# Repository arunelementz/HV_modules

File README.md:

# HV_Module for GM tubes

## Getting started

To make it easy for you to get started with GitLab, here's a list of recommended next steps.

Already a pro? Just edit this README.md and make it your own. Want to make it easy? [Use the template at the bottom](#editing-this-readme)!

## Add your files

- [ ] [Create](https://docs.gitlab.com/ee/user/project/repository/web_editor.html#create-a-file) or [upload](https://docs.gitlab.com/ee/user/project/repository/web_editor.html#upload-a-file) files
- [ ] [Add files using the command line](https://docs.gitlab.com/topics/git/add_files/#add-files-to-a-git-repository) or push an existing Git repository with the following command:

```
cd existing_repo
git remote add origin https://gitlab.com/arunelementz/hv_module-for-gm-tubes.git
git branch -M main
git push -uf origin main
```

## Integrate with your tools

- [ ] [Set up project integrations](https://gitlab.com/arunelementz/hv_module-for-gm-tubes/-/settings/integrations)

## Collaborate with your team

- [ ] [Invite team members and collaborators](https://docs.gitlab.com/ee/user/project/members/)
- [ ] [Create a new merge request](https://docs.gitlab.com/ee/user/project/merge_requests/creating_merge_requests.html)
- [ ] [Automatically close issues from merge requests](https://docs.gitlab.com/ee/user/project/issues/managing_issues.html#closing-issues-automatically)
- [ ] [Enable merge request approvals](https://docs.gitlab.com/ee/user/project/merge_requests/approvals/)
- [ ] [Set auto-merge](https://docs.gitlab.com/user/project/merge_requests/auto_merge/)

## Test and Deploy

Use the built-in continuous integration in GitLab.

- [ ] [Get started with GitLab CI/CD](https://docs.gitlab.com/ee/ci/quick_start/)
- [ ] [Analyze your code for known vulnerabilities with Static Application Security Testing (SAST)](https://docs.gitlab.com/ee/user/application_security/sast/)
- [ ] [Deploy to Kubernetes, Amazon EC2, or Amazon ECS using Auto Deploy](https://docs.gitlab.com/ee/topics/autodevops/requirements.html)
- [ ] [Use pull-based deployments for improved Kubernetes management](https://docs.gitlab.com/ee/user/clusters/agent/)
- [ ] [Set up protected environments](https://docs.gitlab.com/ee/ci/environments/protected_environments.html)

***

# Editing this README

When you're ready to make this README your own, just edit this file and use the handy template below (or feel free to structure it however you want - this is just a starting point!). Thanks to [makeareadme.com](https://www.makeareadme.com/) for this template.

## Suggestions for a good README

Every project is different, so consider which of these sections apply to yours. The sections used in the template are suggestions for most open source projects. Also keep in mind that while a README can be too long and detailed, too long is better than too short. If you think your README is too long, consider utilizing another form of documentation rather than cutting out information.

## Name
Choose a self-explaining name for your project.

## Description
Let people know what your project can do specifically. Provide context and add a link to any reference visitors might be unfamiliar with. A list of Features or a Background subsection can also be added here. If there are alternatives to your project, this is a good place to list differentiating factors.

## Badges
On some READMEs, you may see small images that convey metadata, such as whether or not all the tests are passing for the project. You can use Shields to add some to your README. Many services also have instructions for adding a badge.

## Visuals
Depending on what you are making, it can be a good idea to include screenshots or even a video (you'll frequently see GIFs rather than actual videos). Tools like ttygif can help, but check out Asciinema for a more sophisticated method.

## Installation
Within a particular ecosystem, there may be a common way of installing things, such as using Yarn, NuGet, or Homebrew. However, consider the possibility that whoever is reading your README is a novice and would like more guidance. Listing specific steps helps remove ambiguity and gets people to using your project as quickly as possible. If it only runs in a specific context like a particular programming language version or operating system or has dependencies that have to be installed manually, also add a Requirements subsection.

## Usage
Use examples liberally, and show the expected output if you can. It's helpful to have inline the smallest example of usage that you can demonstrate, while providing links to more sophisticated examples if they are too long to reasonably include in the README.

## Support
Tell people where they can go to for help. It can be any combination of an issue tracker, a chat room, an email address, etc.

## Roadmap
If you have ideas for releases in the future, it is a good idea to list them in the README.

## Contributing
State if you are open to contributions and what your requirements are for accepting them.

For people who want to make changes to your project, it's helpful to have some documentation on how to get started. Perhaps there is a script that they should run or some environment variables that they need to set. Make these steps explicit. These instructions could also be useful to your future self.

You can also document commands to lint the code or run tests. These steps help to ensure high code quality and reduce the likelihood that the changes inadvertently break something. Having instructions for running tests is especially helpful if it requires external setup, such as starting a Selenium server for testing in a browser.

## Authors and acknowledgment
Show your appreciation to those who have contributed to the project.

## License
For open source projects, say how it is licensed.

## Project status
If you have run out of energy or time for your project, put a note at the top of the README saying that development has slowed down or stopped completely. Someone may choose to fork your project or volunteer to step in as a maintainer or owner, allowing your project to keep going. You can also make an explicit request for maintainers.

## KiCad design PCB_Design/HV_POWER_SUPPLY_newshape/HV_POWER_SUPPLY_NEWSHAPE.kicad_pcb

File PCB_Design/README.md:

## HV Schematic and PCB Design Notes

- Schematic is the same as the original **CN0536 board**, including all annotations.
- **Sound notification** is **not included** in the PCB design.
- **BOM** is based on the original **CN0536 BOM**.
- **R19 and R20** are changed to **30 MΩ**  
  - Note: CN0536 BOM specifies **30 MΩ**, but a **different value appears in the schematic** and needs verification.
- **CN0536 stack arrangement** differs and should follow the reference shown.

- **Footprints to be confirmed**:
  - L1  
  - R9  
  - U1  
  - U5
- **Edge cuts** and **high-voltage trace clearance** need to be confirmed.
- **Potentiometer pin numbering** in schematic symbols has been checked.
- **Polygons** are used for drawing copper zones.

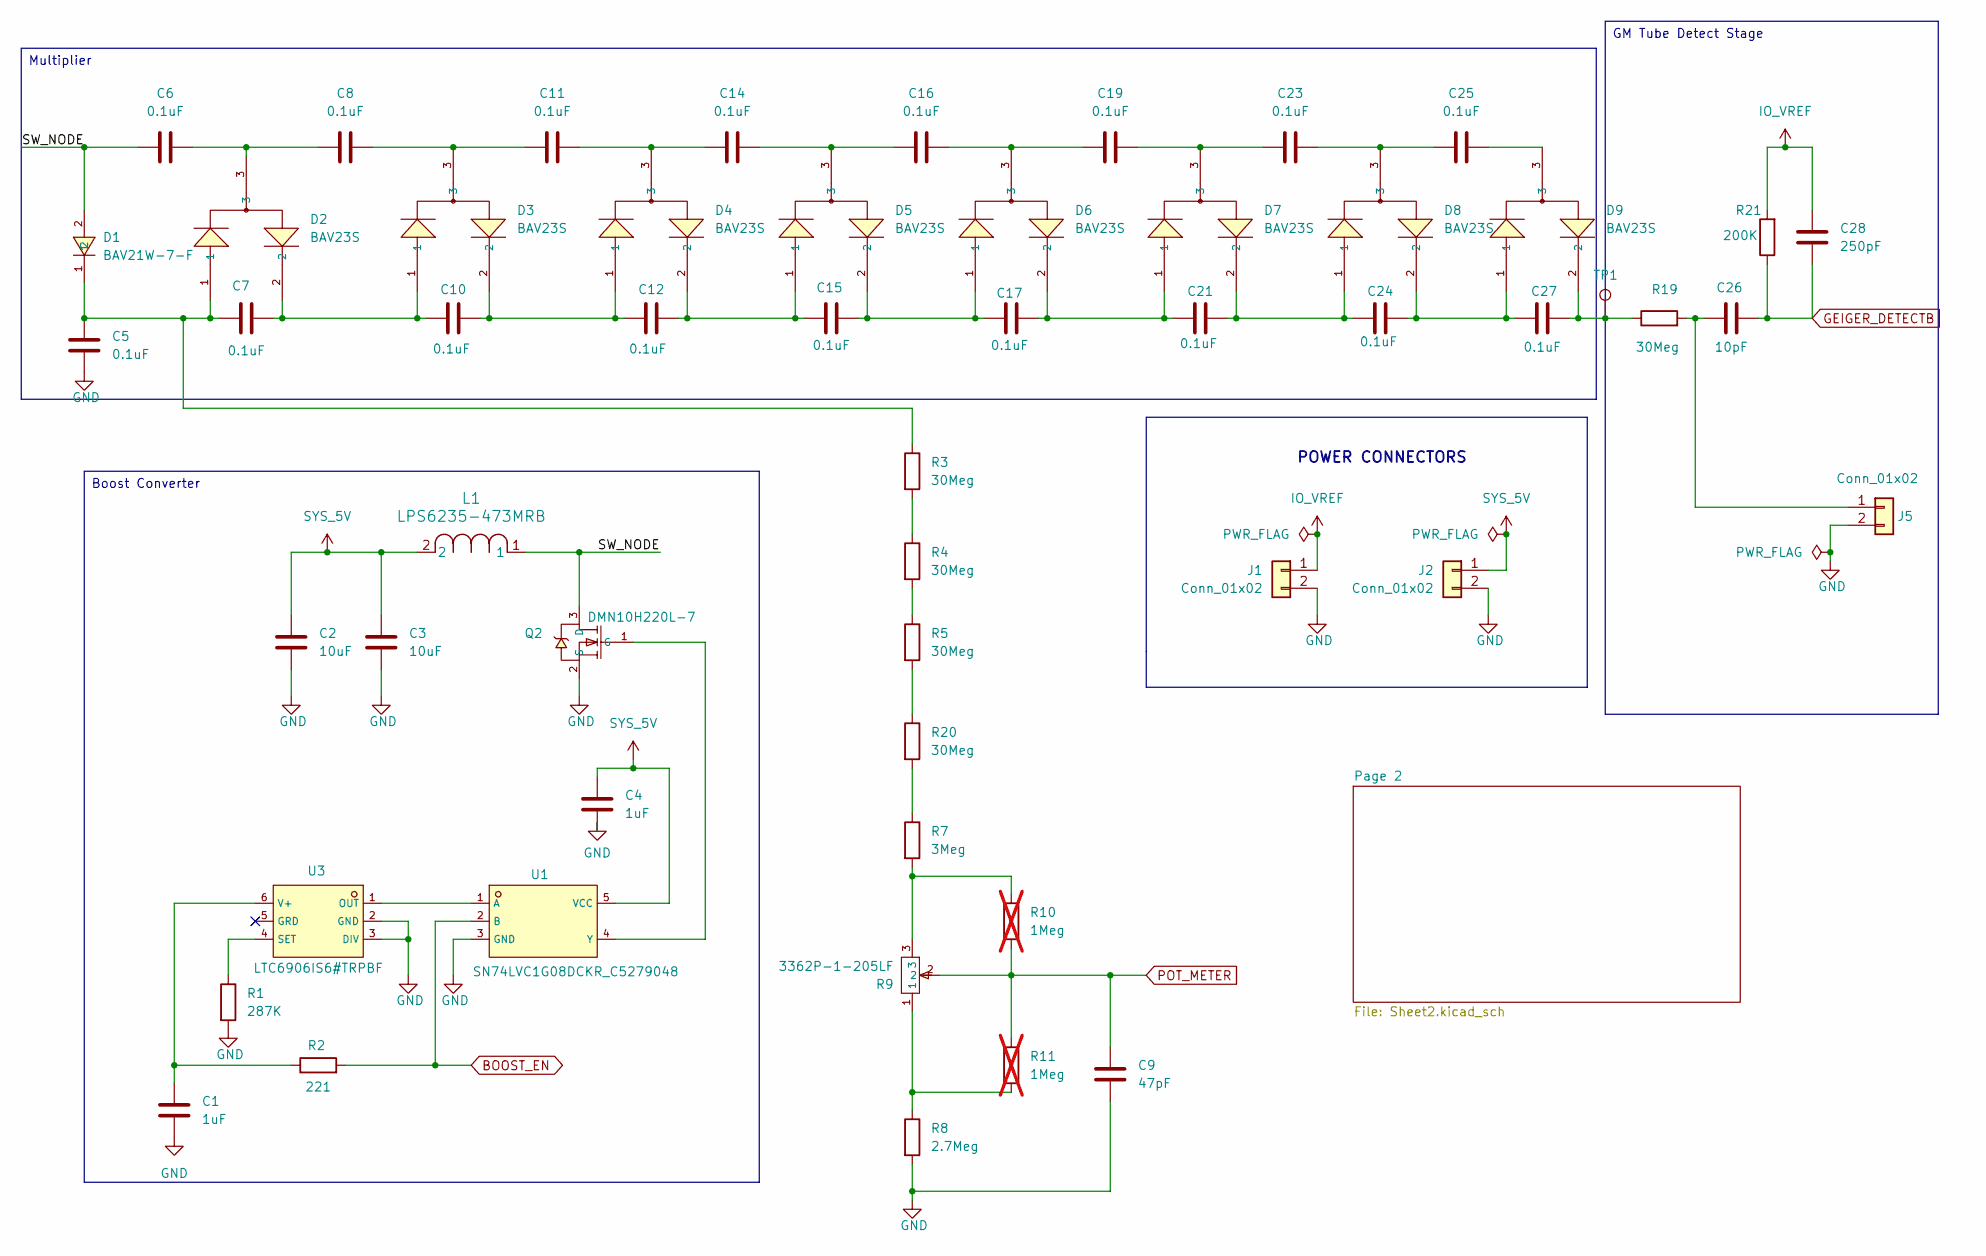
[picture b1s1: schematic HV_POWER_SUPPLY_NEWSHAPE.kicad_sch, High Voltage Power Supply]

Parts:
C1, C4: 1uF; C_0603_1608Metric; manufacturer Part Number 0603YC105KAT2A; LCSC C4153100
C2, C3: 10uF; C_0805_2012Metric; manufacturer Part Number GRM21BR61C106KE15L; LCSC C77075
C5, C6, C7, C8, C10, C11, C12, C14, C15, C16, C17, C19, C21, C23, C24, C25, C27: 0.1uF; C_1206_3216Metric; manufacturer Part Number 12061C104JAT2A; LCSC C597455
C9: 47pF; C_0603_1608Metric; manufacturer Part Number C0603C470K5RACAUTO; LCSC C2169937
C26: 10pF; C_1206_3216Metric; manufacturer Part Number CGA1206C0G100J102MT; LCSC C22374878
C28: 250pF; C_0603_1608Metric; manufacturer Part Number 06033A251JAT2A; Digikey part number 478-11806-2-ND
D1: BAV21W-7-F; SOD-123_L2.8-W1.8-LS3.7-RD; manufacturer Part Number BAV21WS-7-F; LCSC C155214
D2, D3, D4, D5, D6, D7, D8, D9: BAV23S; BAV23S_SOT-23-3_L2.9-W1.6-P1.90-LS2.8-BR; manufacturer Part Number BAV23S; LCSC C151049
J1, J2, J5: Conn_01x02; PinHeader_1x02_P2.54mm_Vertical; manufacturer Part Number PH1-02-UA; LCSC C5828287
L1: LPS6235-473MRB; LPS6235473MRB; manufacturer Part Number LPS6235-473MRC; Mouser Number 994-LPS6235-473MRB
Q2: DMN10H220L-7; SOT-23-3_L2.9-W1.6-P1.90-LS2.8-BR; manufacturer Part Number DMN10H220L-7; LCSC C102615
R1: 287K; R_0603_1608Metric; manufacturer Part Number RC0603FR-07287KL; LCSC C245944
R2: 221; R_0805_2012Metric; manufacturer Part Number TP0805B221RP0510Z; LCSC C5184183
R3, R4, R5, R19, R20: 30Meg; R_0805_2012Metric; manufacturer Part Number HVCB0805FDC30M0; LCSC HVCB0805FDC30M0
R7: 3Meg; R_0603_1608Metric; manufacturer Part Number CRCW06033M00FKEA; LCSC C4299696
R8: 2.7Meg; R_0603_1608Metric; manufacturer Part Number FRC0805F2704TS; LCSC C403468
R9: 3362P-1-205LF; RES-ADJ-TH_3362P; manufacturer Part Number 3362P-1-205LF; LCSC C124582
R10, R11: 1Meg; R_0603_1608Metric; manufacturer Part Number RC0805FR-071ML; LCSC C107700; not fitted
R21: 200K; R_0603_1608Metric; manufacturer Part Number ERJ3EKF2003V; LCSC C118142
TP1: TestPoint; TestPoint_Pad_1.0x1.0mm
U1: SN74LVC1G08DCKR_C5279048; SC-70-5_L2.0-W1.3-P0.65-LS2.1-BR; manufacturer Part Number SN74LVC1G08DCKR; LCSC C7832
U3: LTC6906IS6#TRPBF; TSOT-23-6_L2.9-W1.6-P0.95-LS2.8-BR; manufacturer Part Number LTC6906IS6#TRMPBF; LCSC C581017

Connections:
/SW_NODE: C6.1, D1.2, L1.1, Q2.3 (D)
BOOST_EN: R2.2, U1.2 (B); also elsewhere on the board
GEIGER_DETECTB: C26.2, C28.1, R21.1; also elsewhere on the board
GND: C1.2, C2.2, C3.2, C4.2, C5.2, C9.2, J1.2, J2.2, J5.2, Q2.2 (S), R1.2, R8.2, U1.3 (GND), U3.2 (GND), U3.3 (DIV); also elsewhere on the board
IO_VREF: C28.2, J1.1, R21.2; also elsewhere on the board
unnamed: C5.1, C7.1, D1.1, D2.1, R3.1
unnamed: C6.2, C8.1, D2.3
unnamed: C7.2, C10.1, D2.2, D3.1
unnamed: C10.2, C12.1, D3.2, D4.1
unnamed: C8.2, C11.1, D3.3
unnamed: C11.2, C14.1, D4.3
unnamed: C12.2, C15.1, D4.2, D5.1
unnamed: C14.2, C16.1, D5.3
unnamed: C15.2, C17.1, D5.2, D6.1
unnamed: C16.2, C19.1, D6.3
unnamed: C17.2, C21.1, D6.2, D7.1
unnamed: C19.2, C23.1, D7.3
unnamed: C21.2, C24.1, D7.2, D8.1
unnamed: C23.2, C25.1, D8.3
unnamed: C24.2, C27.1, D8.2, D9.1
unnamed: C25.2, D9.3
unnamed: C27.2, D9.2, R19.1, TP1.1
unnamed: C26.1, J5.1, R19.2
unnamed: Q2.1 (G), U1.4 (Y)
unnamed: R3.2, R4.1
unnamed: R4.2, R5.1
unnamed: R7.2, R9.3, R10.1
unnamed: R8.1, R9.1, R11.2
unnamed: R5.2, R20.1
unnamed: R7.1, R20.2
unnamed: U1.1 (A), U3.1 (OUT)
unnamed: R1.1, U3.4 (SET)
unnamed: C1.1, R2.1, U3.6 (V+)
POT_METER: C9.1, R9.2, R10.2, R11.1; also elsewhere on the board
SYS_5V: C2.1, C3.1, C4.1, J2.1, L1.2, U1.5 (VCC); also elsewhere on the board

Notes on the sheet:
POWER CONNECTORS
Boost Converter
GM Tube Detect Stage
Multiplier

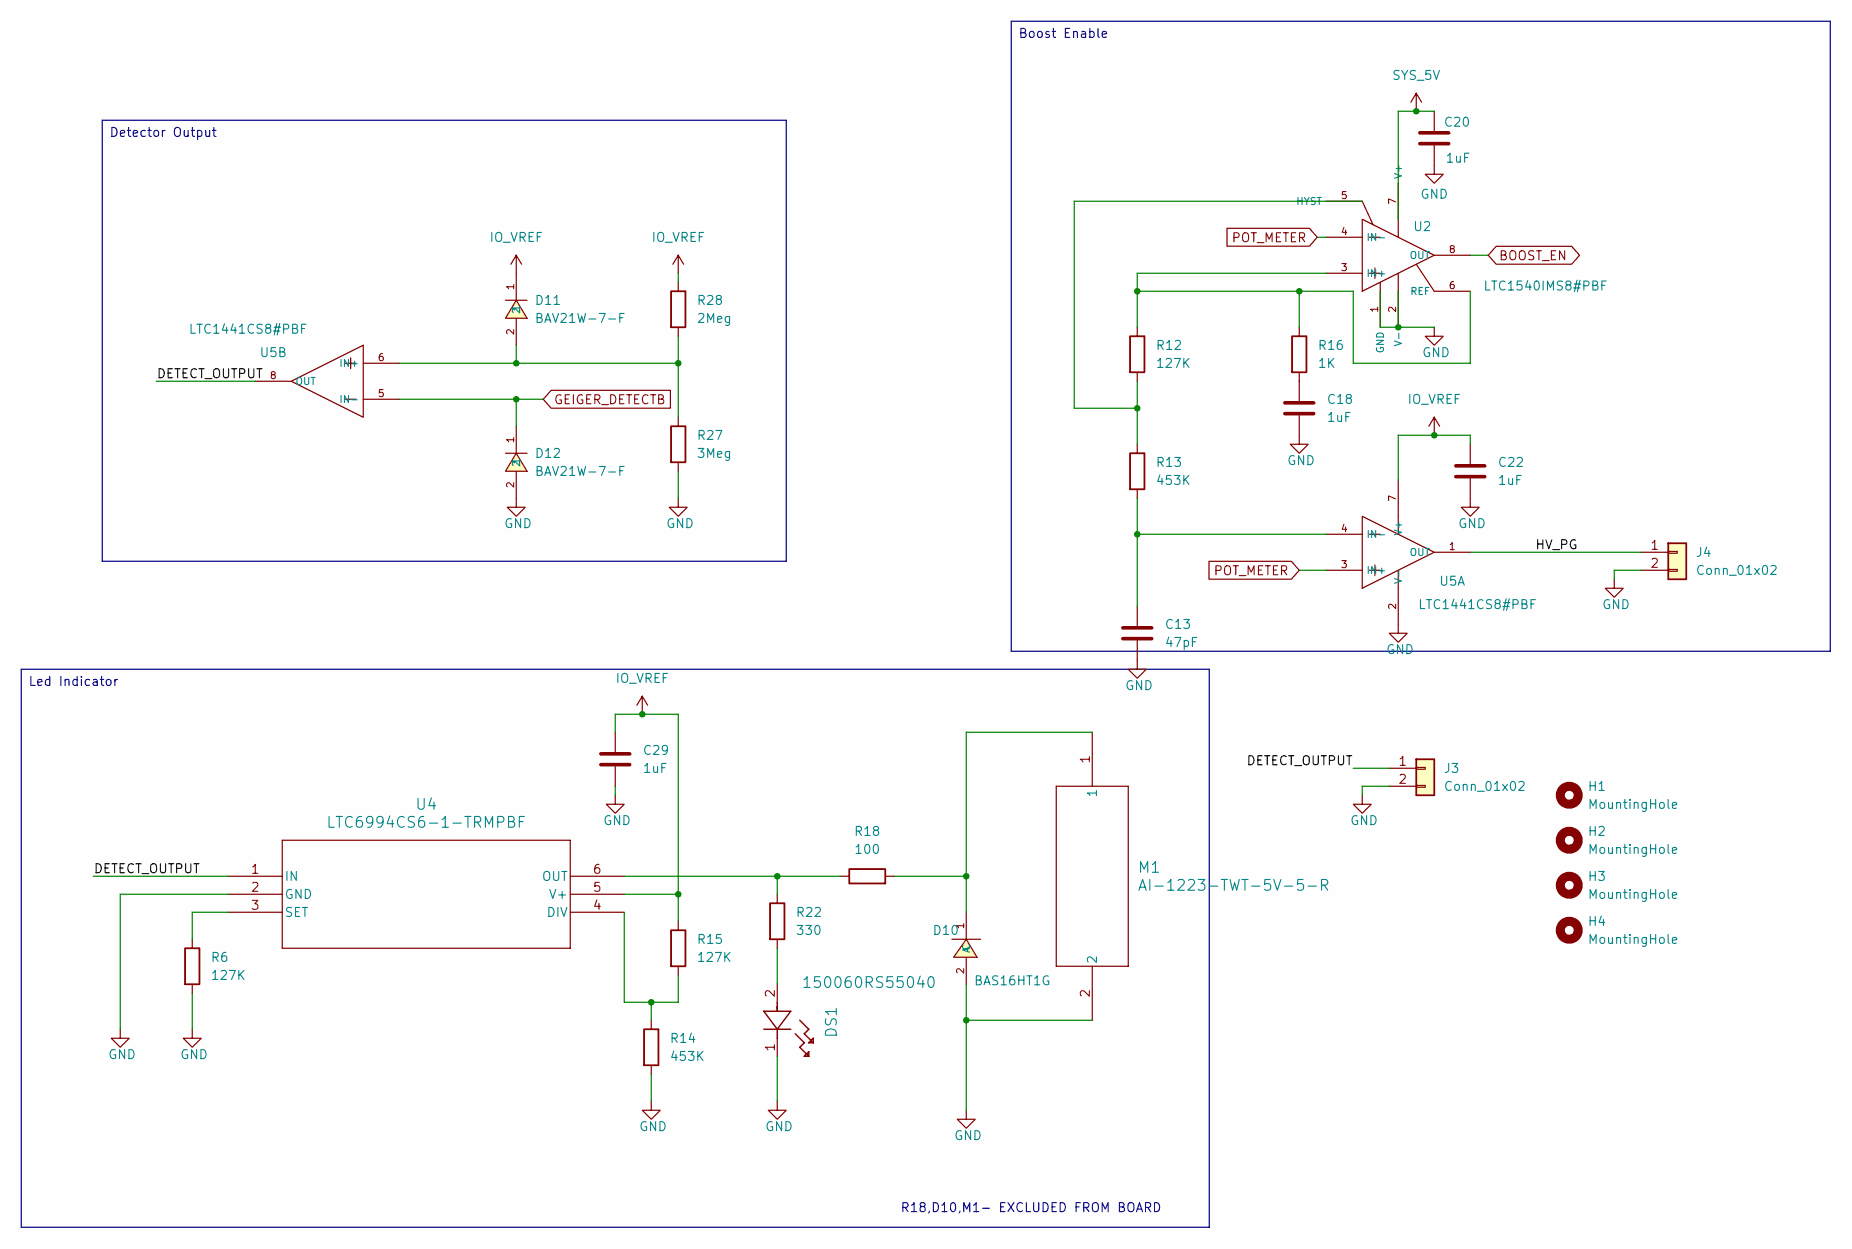
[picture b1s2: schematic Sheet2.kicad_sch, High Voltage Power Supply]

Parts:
C13: 47pF; C_0603_1608Metric; manufacturer Part Number C0603C470K5RACAUTO; LCSC C2169937
C18, C20, C22, C29: 1uF; C_0603_1608Metric; manufacturer Part Number 0603YC105KAT2A; LCSC C4153100
D10: BAS16HT1G; SOD-323_L1.8-W1.3-LS2.5-RD; manufacturer Part Number BAS16HT1G; LCSC C131148
D11, D12: BAV21W-7-F; SOD-123_L2.8-W1.8-LS3.7-RD; manufacturer Part Number BAV21WS-7-F; LCSC C155214
DS1: 150060RS55040; LED_0603_1608Metric; manufacturer Part Number 150060RS55040; LCSC C6067128
H1, H2, H3, H4: MountingHole; MountingHole_3.2mm_M3
J3, J4: Conn_01x02; PinHeader_1x02_P2.54mm_Vertical; manufacturer Part Number PH1-02-UA; LCSC C5828287
M1: AI-1223-TWT-5V-5-R; AI-1223-TWT-5V-5-R_PUI; manufacturer Part Number AI-1223-TWT-5V-5-R; LCSC C5250722
R6, R12, R15: 127K; R_0603_1608Metric; manufacturer Part Number RC0603FR-07127KL; LCSC C245905
R13, R14: 453K; R_0603_1608Metric; manufacturer Part Number RC0603FR-07453KL; LCSC C273765
R16: 1K; R_0603_1608Metric; manufacturer Part Number RC0603FR-071KL; LCSC C22548
R18: 100; R_0603_1608Metric; manufacturer Part Number 0805W8F1000T5E; LCSC C17408
R22: 330; R_0603_1608Metric; manufacturer Part Number 0603WAJ0331T5E; LCSC C25231
R27: 3Meg; R_0603_1608Metric; manufacturer Part Number CRCW06033M00FKEA; LCSC C4299696
R28: 2Meg; R_0603_1608Metric; manufacturer Part Number RC0603FR-072ML; LCSC C114615
U2: LTC1540IMS8#PBF; MSOP-8_L3.0-W3.0-P0.65-LS4.9-BL; manufacturer Part Number LTC1540IMS8#PBF; LCSC C580397
U4: LTC6994CS6-1-TRMPBF; TSOT-23_S6_LIT; manufacturer Part Number LTC6994CS6-1#TRMPBF; LCSC C581050
U5: LTC1441CS8#PBF; SOIC-8_L4.9-W3.8-P1.27-LS6.0-BL; manufacturer Part Number LTC1441CS8#PBF; LCSC C675522

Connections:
/Page 2/DETECT_OUTPUT: J3.1, U4.1 (IN), U5.8 (OUT)
/Page 2/HV_PG: J4.1, U5.1 (OUT)
BOOST_EN: U2.8 (OUT); also elsewhere on the board
GEIGER_DETECTB: D12.1, U5.5 (IN-); also elsewhere on the board
GND: C13.2, C18.2, C20.2, C22.2, C29.2, D10.2 (A), D12.2, DS1.1, J3.2, J4.2, M1.2, R6.2, R14.2, R27.2, U2.1 (GND), U2.2 (V-), U4.2 (GND), U5.2 (V-); also elsewhere on the board
IO_VREF: C22.1, C29.1, D11.1, R15.1, R28.1, U4.5 (V+), U5.7 (V+); also elsewhere on the board
unnamed: C18.1, R16.2
unnamed: D10.1 (C), M1.1, R18.2
unnamed: DS1.2, R22.2
unnamed: R12.2, R13.1, U2.5 (HYST)
unnamed: R12.1, R16.1, U2.3 (IN+), U2.6 (REF)
unnamed: R14.1, R15.2, U4.4 (DIV)
unnamed: R18.1, R22.1, U4.6 (OUT)
unnamed: R6.1, U4.3 (SET)
unnamed: C13.1, R13.2, U5.4 (IN-)
unnamed: D11.2, R27.1, R28.2, U5.6 (IN+)
POT_METER: U2.4 (IN-), U5.3 (IN+); also elsewhere on the board
SYS_5V: C20.1, U2.7 (V+); also elsewhere on the board

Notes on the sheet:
R18,D10,M1- EXCLUDED FROM BOARD
Detector Output
Boost Enable
Led Indicator

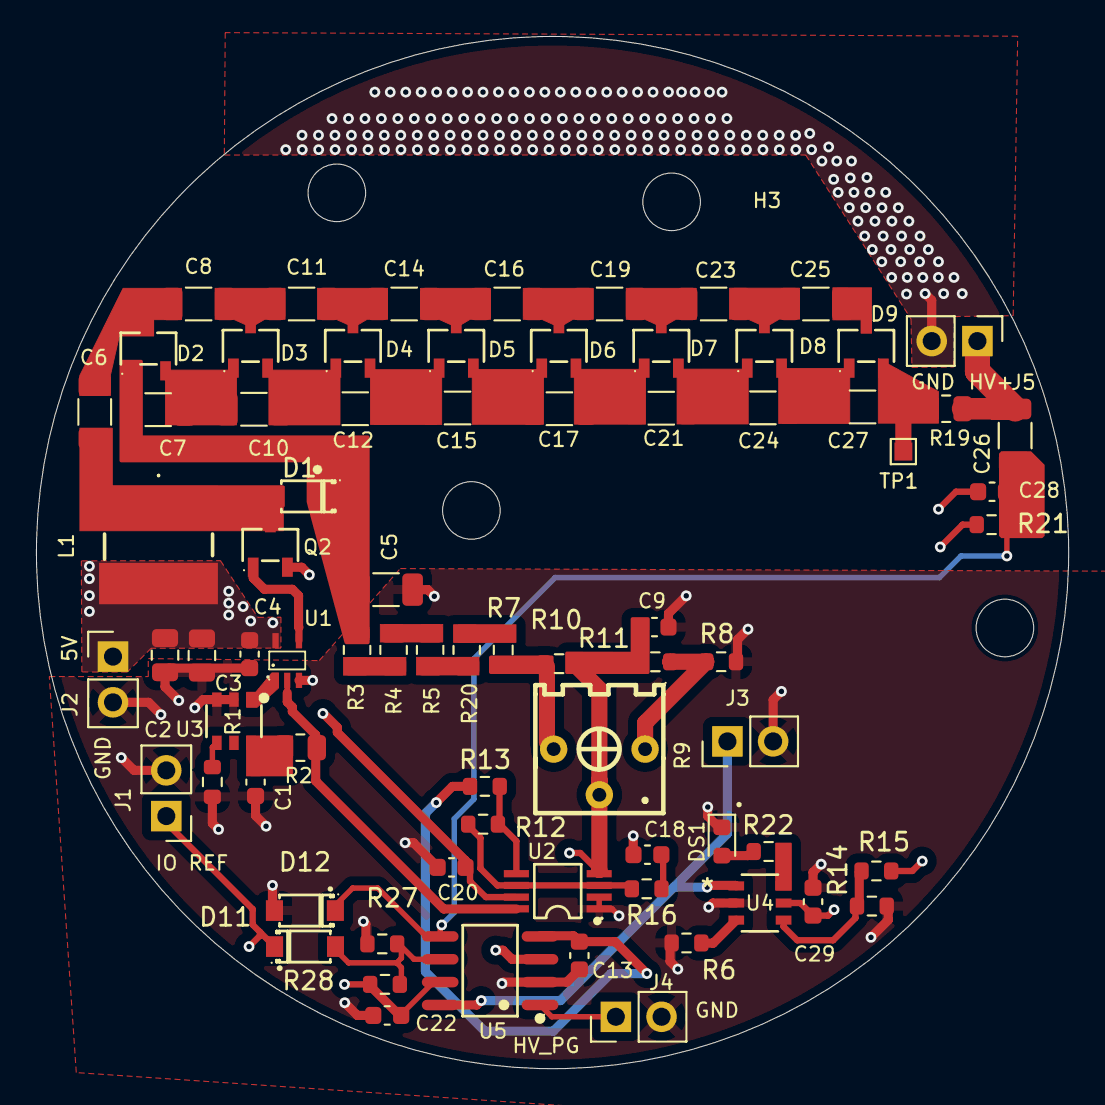
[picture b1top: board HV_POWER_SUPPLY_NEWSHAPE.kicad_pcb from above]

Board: 4 copper layers, 57.3 x 57.3 mm, 80 parts (0 on the bottom side), 46 nets.

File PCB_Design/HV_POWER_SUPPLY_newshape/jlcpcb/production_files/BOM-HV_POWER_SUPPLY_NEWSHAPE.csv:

Comment,Designator,Footprint,LCSC,Quantity
0.1uF,"C10,C11,C12,C14,C15,C16,C17,C19,C21,C23,C24,C25,C27,C5,C6,C7,C8",C_1206_3216Metric,C597455,17
10pF,C26,C_1206_3216Metric,C22374878,1
10uF,"C2,C3",C_0805_2012Metric,C77075,2
127K,"R12,R15",R_0603_1608Metric,C228282,2
127K,R6,R_0603_1608Metric,C245905,1
1K,R16,R_0603_1608Metric,C22548,1
1uF,"C1,C18,C20,C22,C29,C4",C_0603_1608Metric,C4153100,6
2.7Meg,R8,R_0603_1608Metric,C403468,1
200K,R21,R_0603_1608Metric,C118142,1
221,R2,R_0805_2012Metric,C5184183,1
250pF,C28,C_0603_1608Metric,C2169911,1
287K,R1,R_0603_1608Metric,C245944,1
2Meg,R28,R_0603_1608Metric,C114615,1
30Meg,"R19,R20,R3,R4,R5",R_0805_2012Metric,C2641377,5
330,R22,R_0603_1608Metric,C25231,1
3362P-1-205LF,R9,RES-ADJ-TH_3362P,C124582,1
3Meg,"R27,R7",R_0603_1608Metric,C4299696,2
453K,"R13,R14",R_0603_1608Metric,C273765,2
47pF,"C13,C9",C_0603_1608Metric,C2169937,2
BAV21W-7-F,"D1,D11,D12",SOD-123_L2.8-W1.8-LS3.7-RD,C155214,3
BAV23S,"D2,D3,D4,D5,D6,D7,D8,D9",BAV23S_SOT-23-3_L2.9-W1.6-P1.90-LS2.8-BR,C151049,8
Conn_01x02,"J1,J2,J3,J4,J5",PinHeader_1x02_P2.54mm_Vertical,C5828287,5
DMN10H220L-7,Q2,SOT-23-3_L2.9-W1.6-P1.90-LS2.8-BR,C102615,1
LPS6235-473MRB,L1,LPS6235473MRB,C3911705,1
LTC1441CS8#PBF,U5,SOIC-8_L4.9-W3.8-P1.27-LS6.0-BL,C675522,1
LTC1540IMS8#PBF,U2,MSOP-8_L3.0-W3.0-P0.65-LS4.9-BL,C580397,1
LTC6906IS6#TRPBF,U3,TSOT-23-6_L2.9-W1.6-P0.95-LS2.8-BR,C581017,1
LTC6994CS6-1-TRMPBF,U4,TSOT-23_S6_LIT,C581050,1
SN74LVC1G08DCKR_C5279048,U1,SC-70-5_L2.0-W1.3-P0.65-LS2.1-BR,C7832,1
TLMS1000-GS08,DS1,LED_0603_1608Metric,C2286,1
TestPoint,TP1,TestPoint_Pad_1.0x1.0mm,,1

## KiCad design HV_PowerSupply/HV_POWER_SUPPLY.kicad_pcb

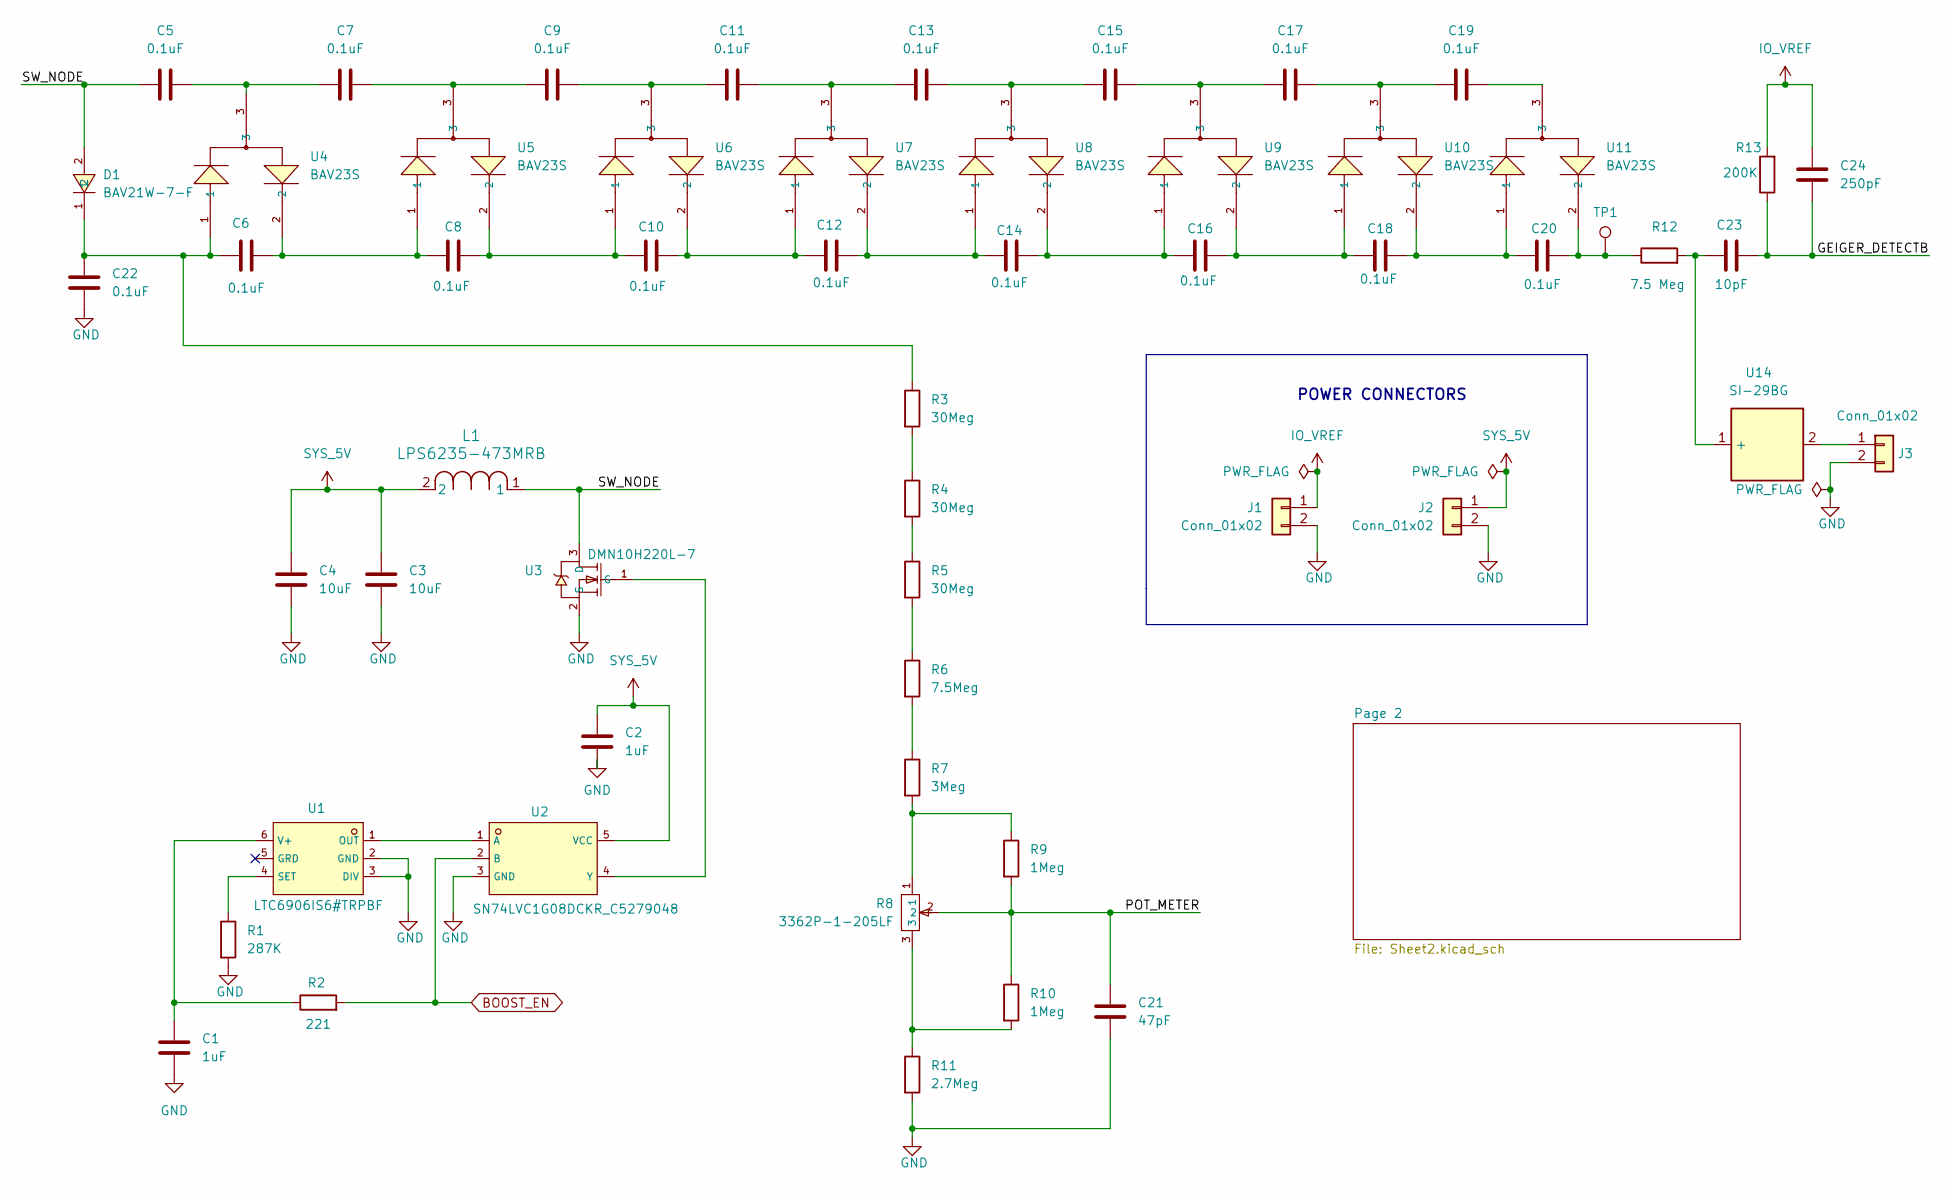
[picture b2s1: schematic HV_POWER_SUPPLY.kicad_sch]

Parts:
C1, C2: 1uF; C_0603_1608Metric; manufacturer Part Number CL10A105KB8NNNC; LCSC C15849
C3, C4: 10uF; C_0805_2012Metric; manufacturer Part Number CL21A106KAYNNNE; LCSC C15850
C5, C6, C7, C8, C9, C10, C11, C12, C13, C14, C15, C16, C17, C18, C19, C20, C22: 0.1uF; C_1206_3216Metric; manufacturer Part Number CL31B104KBCNNNC; LCSC C24497
C21: 47pF; C_0603_1608Metric; manufacturer Part Number 0603X476M6R3NT; LCSC C178330
C23: 10pF; C_1206_3216Metric; manufacturer Part Number TCC1206COG100J102DT; LCSC C377014
C24: 250pF; C_0603_1608Metric; manufacturer Part Number 06033A251JAT2A; Digikey part number 478-11806-2-ND
D1: BAV21W-7-F; SOD-323_L1.8-W1.3-LS2.5-RD; manufacturer Part Number BAV21WS-7-F; LCSC C151350
J1, J2, J3: Conn_01x02; PinHeader_1x02_P2.54mm_Vertical
L1: LPS6235-473MRB; LPS6235473MRB; manufacturer Part Number LPS6235-473MRB; Mouser Number 994-LPS6235-473MRB
R1: 287K; R_0603_1608Metric; manufacturer Part Number 0603WAF2873T5E; LCSC C22972
R2: 221; R_0805_2012Metric; manufacturer Part Number CR0805-FX-2210ELF; LCSC C204308
R3, R4, R5: 30Meg; R_0805_2012Metric; manufacturer Part Number FHW0805UC2N2KGT; LCSC C317991
R6: 7.5Meg; R_0805_2012Metric; manufacturer Part Number FRC0805J755 TS; LCSC C2933569
R7: 3Meg; R_0805_2012Metric; manufacturer Part Number FRC0805J305 TS; LCSC C2907325
R8: 3362P-1-205LF; RES-ADJ-TH_3362P; manufacturer Part Number 3362P-1-205LF; LCSC C124582
R9, R10: 1Meg; R_0805_2012Metric; manufacturer Part Number RC0805FR-071ML; LCSC C107700
R11: 2.7Meg; R_0805_2012Metric; manufacturer Part Number FRC0805F2704TS; LCSC C2933390
R12: 7.5 Meg; R_0805_2012Metric; manufacturer Part Number FRC0805J755 TS; LCSC C2933569
R13: 200K; R_0805_2012Metric; manufacturer Part Number 0805W8F2003T5E; LCSC C17539
TP1: TestPoint; TestPoint_Pad_1.0x1.0mm
U1: LTC6906IS6#TRPBF; TSOT-23-6_L2.9-W1.6-P0.95-LS2.8-BR; manufacturer Part Number LTC6906IS6#TRPBF; LCSC C689638
U2: SN74LVC1G08DCKR_C5279048; SC-70-5_L2.0-W1.3-P0.65-LS2.1-BR; manufacturer Part Number SN74LVC1G08DCKR; LCSC C5279048
U3: DMN10H220L-7; SOT-23-3_L2.9-W1.6-P1.90-LS2.8-BR; manufacturer Part Number DMN10H220L-7; LCSC C102615
U4, U5, U6, U7, U8, U9, U10, U11: BAV23S; BAV23S_SOT-23-3_L2.9-W1.6-P1.90-LS2.8-BR; manufacturer Part Number BAV23S; LCSC C44345
U14: SI-29BG

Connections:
/GEIGER_DETECTB: C23.2, C24.1, R13.1
/POT_METER: C21.1, R8.2, R9.2, R10.1
/SW_NODE: C5.1, D1.2, L1.1, U3.3 (D)
BOOST_EN: R2.2, U2.2 (B); also elsewhere on the board
GND: C1.2, C2.2, C3.2, C4.2, C21.2, C22.2, J1.2, J2.2, J3.2, R1.2, R11.2, U1.2 (GND), U1.3 (DIV), U2.3 (GND), U3.2 (S); also elsewhere on the board
IO_VREF: C24.2, J1.1, R13.2; also elsewhere on the board
unnamed: C5.2, C7.1, U4.3
unnamed: C6.2, C8.1, U4.2, U5.1
unnamed: C7.2, C9.1, U5.3
unnamed: C8.2, C10.1, U5.2, U6.1
unnamed: C10.2, C12.1, U6.2, U7.1
unnamed: C9.2, C11.1, U6.3
unnamed: C11.2, C13.1, U7.3
unnamed: C12.2, C14.1, U7.2, U8.1
unnamed: C13.2, C15.1, U8.3
unnamed: C14.2, C16.1, U8.2, U9.1
unnamed: C15.2, C17.1, U9.3
unnamed: C16.2, C18.1, U9.2, U10.1
unnamed: C17.2, C19.1, U10.3
unnamed: C18.2, C20.1, U10.2, U11.1
unnamed: C19.2, U11.3
unnamed: C20.2, R12.1, TP1.1, U11.2
unnamed: C6.1, C22.1, D1.1, R3.1, U4.1
unnamed: J3.1, U14.2
unnamed: R3.2, R4.1
unnamed: R4.2, R5.1
unnamed: R5.2, R6.1
unnamed: R6.2, R7.1
unnamed: R7.2, R8.1, R9.1
unnamed: R8.3, R10.2, R11.1
unnamed: U1.1 (OUT), U2.1 (A)
unnamed: R1.1, U1.4 (SET)
unnamed: C1.1, R2.1, U1.6 (V+)
unnamed: U2.4 (Y), U3.1 (G)
unnamed: C23.1, R12.2, U14.1 (+)
SYS_5V: C2.1, C3.1, C4.1, J2.1, L1.2, U2.5 (VCC); also elsewhere on the board

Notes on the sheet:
POWER CONNECTORS

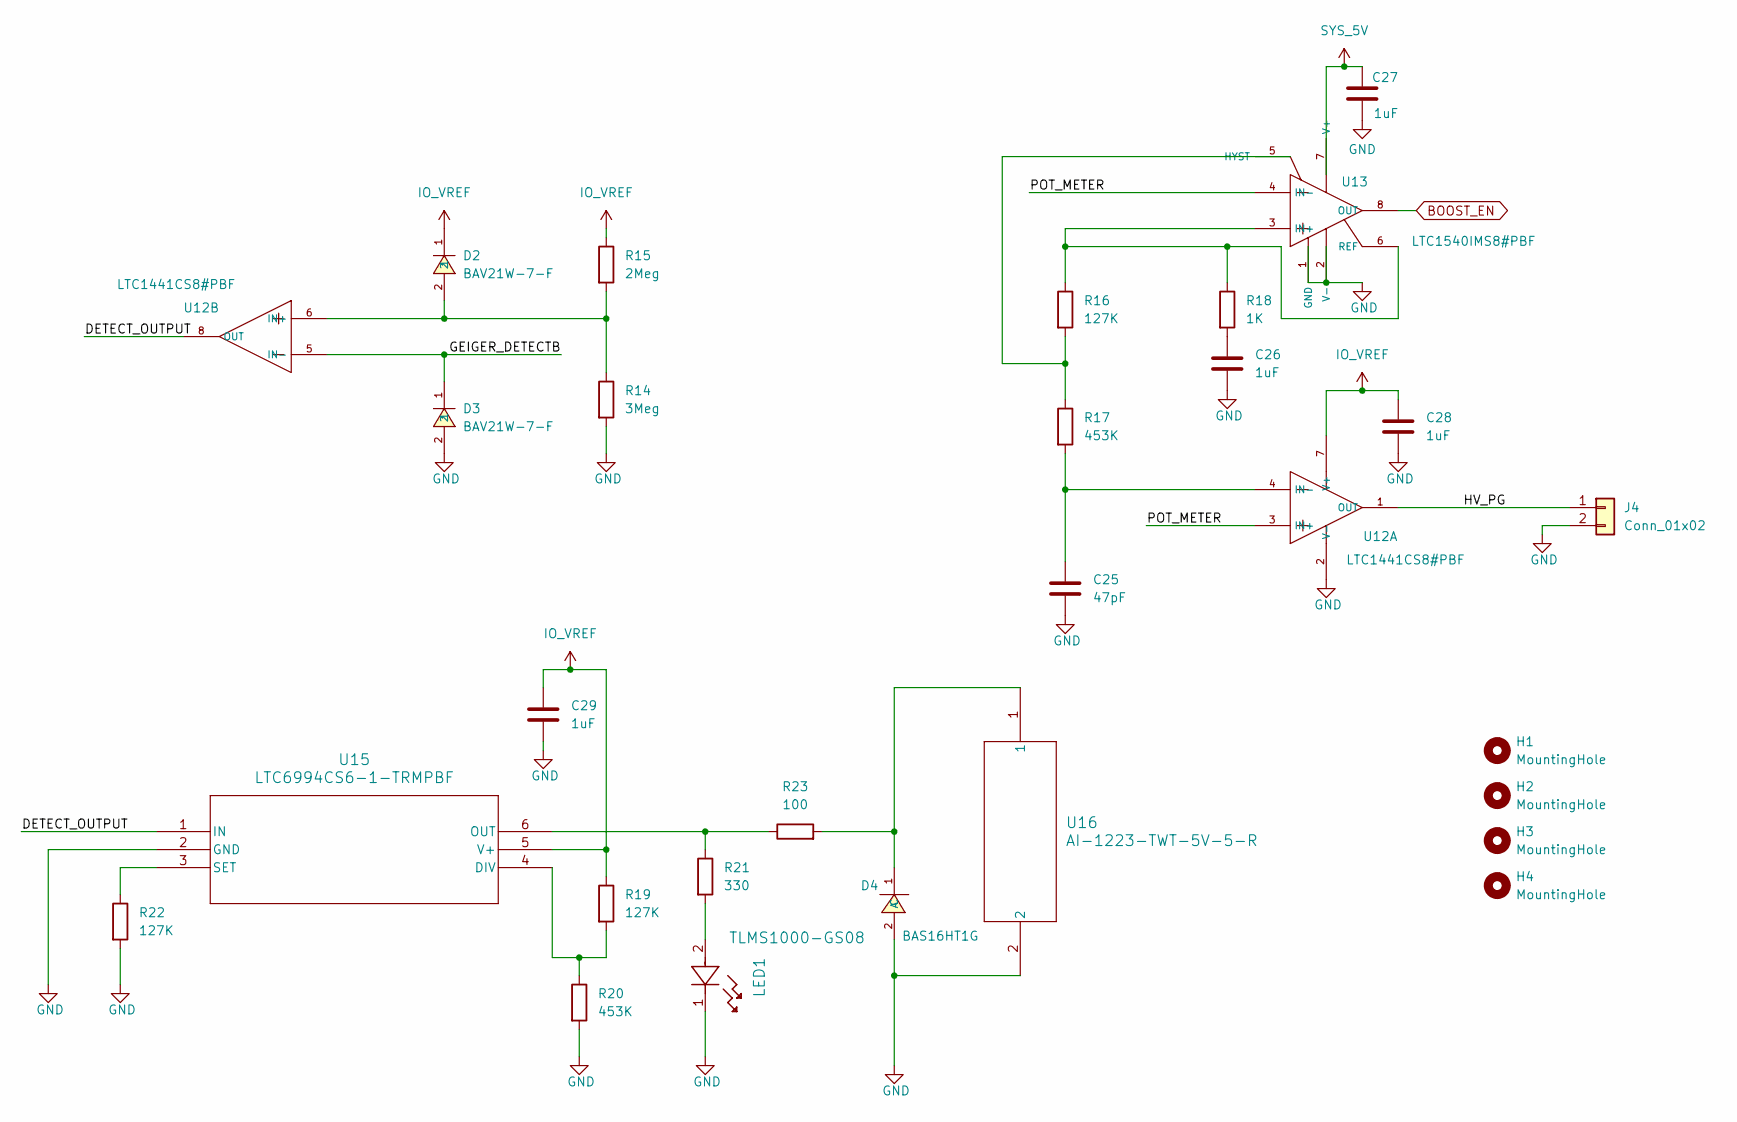
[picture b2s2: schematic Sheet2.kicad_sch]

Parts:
C25: 47pF; C_0603_1608Metric; manufacturer Part Number 0603X476M6R3NT; LCSC C178330
C26, C27, C28, C29: 1uF; C_0603_1608Metric; manufacturer Part Number CL10A105KB8NNNC; LCSC C15849
D2, D3: BAV21W-7-F; SOD-323_L1.8-W1.3-LS2.5-RD; manufacturer Part Number BAV21WS-7-F; LCSC C151350
D4: BAS16HT1G; SOD-323_L1.8-W1.3-LS2.5-RD; manufacturer Part Number BAS16HT1G; LCSC C131148
H1, H2, H3, H4: MountingHole; MountingHole_3.2mm_M3
J4: Conn_01x02; PinHeader_1x02_P2.54mm_Vertical
LED1: TLMS1000-GS08; LED_0603_1608Metric; manufacturer Part Number KT-0603R; LCSC C2286
R14: 3Meg; R_0805_2012Metric; manufacturer Part Number FRC0805J305 TS; LCSC C2907325
R15: 2Meg; R_0805_2012Metric; manufacturer Part Number 0805W8F2004T5E; LCSC C26112
R16, R19, R22: 127K; R_0805_2012Metric; manufacturer Part Number AC0805FR-07127KL; LCSC C228282
R17, R20: 453K; R_0805_2012Metric; manufacturer Part Number UNI-ROYAL(Uniroyal Elec); LCSC C17702
R18: 1K; R_0805_2012Metric; manufacturer Part Number RC0805JR-071KL; LCSC C100046
R21: 330; R_0805_2012Metric; manufacturer Part Number 0805W8F3300T5E; LCSC C17630
R23: 100; R_0805_2012Metric; manufacturer Part Number 0805W8F1000T5E; LCSC C17408
U12: LTC1441CS8#PBF; SOIC-8_L4.9-W3.8-P1.27-LS6.0-BL; manufacturer Part Number LTC1441CS8#PBF; LCSC C675522
U13: LTC1540IMS8#PBF; MSOP-8_L3.0-W3.0-P0.65-LS4.9-BL; manufacturer Part Number LTC1540IMS8#PBF; LCSC C580397
U15: LTC6994CS6-1-TRMPBF; TSOT-23_S6_LIT; manufacturer Part Number LTC6994CS6-1#TRMPBF; LCSC C581050
U16: AI-1223-TWT-5V-5-R; AI-1223-TWT-5V-5-R_PUI; manufacturer Part Number AI-1223-TWT-5V-5-R; LCSC C5250722

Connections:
/Page 2/DETECT_OUTPUT: U12.8 (OUT), U15.1 (IN)
/Page 2/GEIGER_DETECTB: D3.1, U12.5 (IN-)
/Page 2/HV_PG: J4.1, U12.1 (OUT)
/Page 2/POT_METER: U12.3 (IN+), U13.4 (IN-)
BOOST_EN: U13.8 (OUT); also elsewhere on the board
GND: C25.2, C26.2, C27.2, C28.2, C29.2, D3.2, D4.2 (A), J4.2, LED1.1, R14.2, R20.2, R22.2, U12.2 (V-), U13.1 (GND), U13.2 (V-), U15.2 (GND), U16.2; also elsewhere on the board
IO_VREF: C28.1, C29.1, D2.1, R15.1, R19.1, U12.7 (V+), U15.5 (V+); also elsewhere on the board
unnamed: C26.1, R18.2
unnamed: D4.1 (C), R23.2, U16.1
unnamed: LED1.2, R21.2
unnamed: C25.1, R17.2, U12.4 (IN-)
unnamed: D2.2, R14.1, R15.2, U12.6 (IN+)
unnamed: R16.2, R17.1, U13.5 (HYST)
unnamed: R16.1, R18.1, U13.3 (IN+), U13.6 (REF)
unnamed: R19.2, R20.1, U15.4 (DIV)
unnamed: R21.1, R23.1, U15.6 (OUT)
unnamed: R22.1, U15.3 (SET)
SYS_5V: C27.1, U13.7 (V+); also elsewhere on the board
